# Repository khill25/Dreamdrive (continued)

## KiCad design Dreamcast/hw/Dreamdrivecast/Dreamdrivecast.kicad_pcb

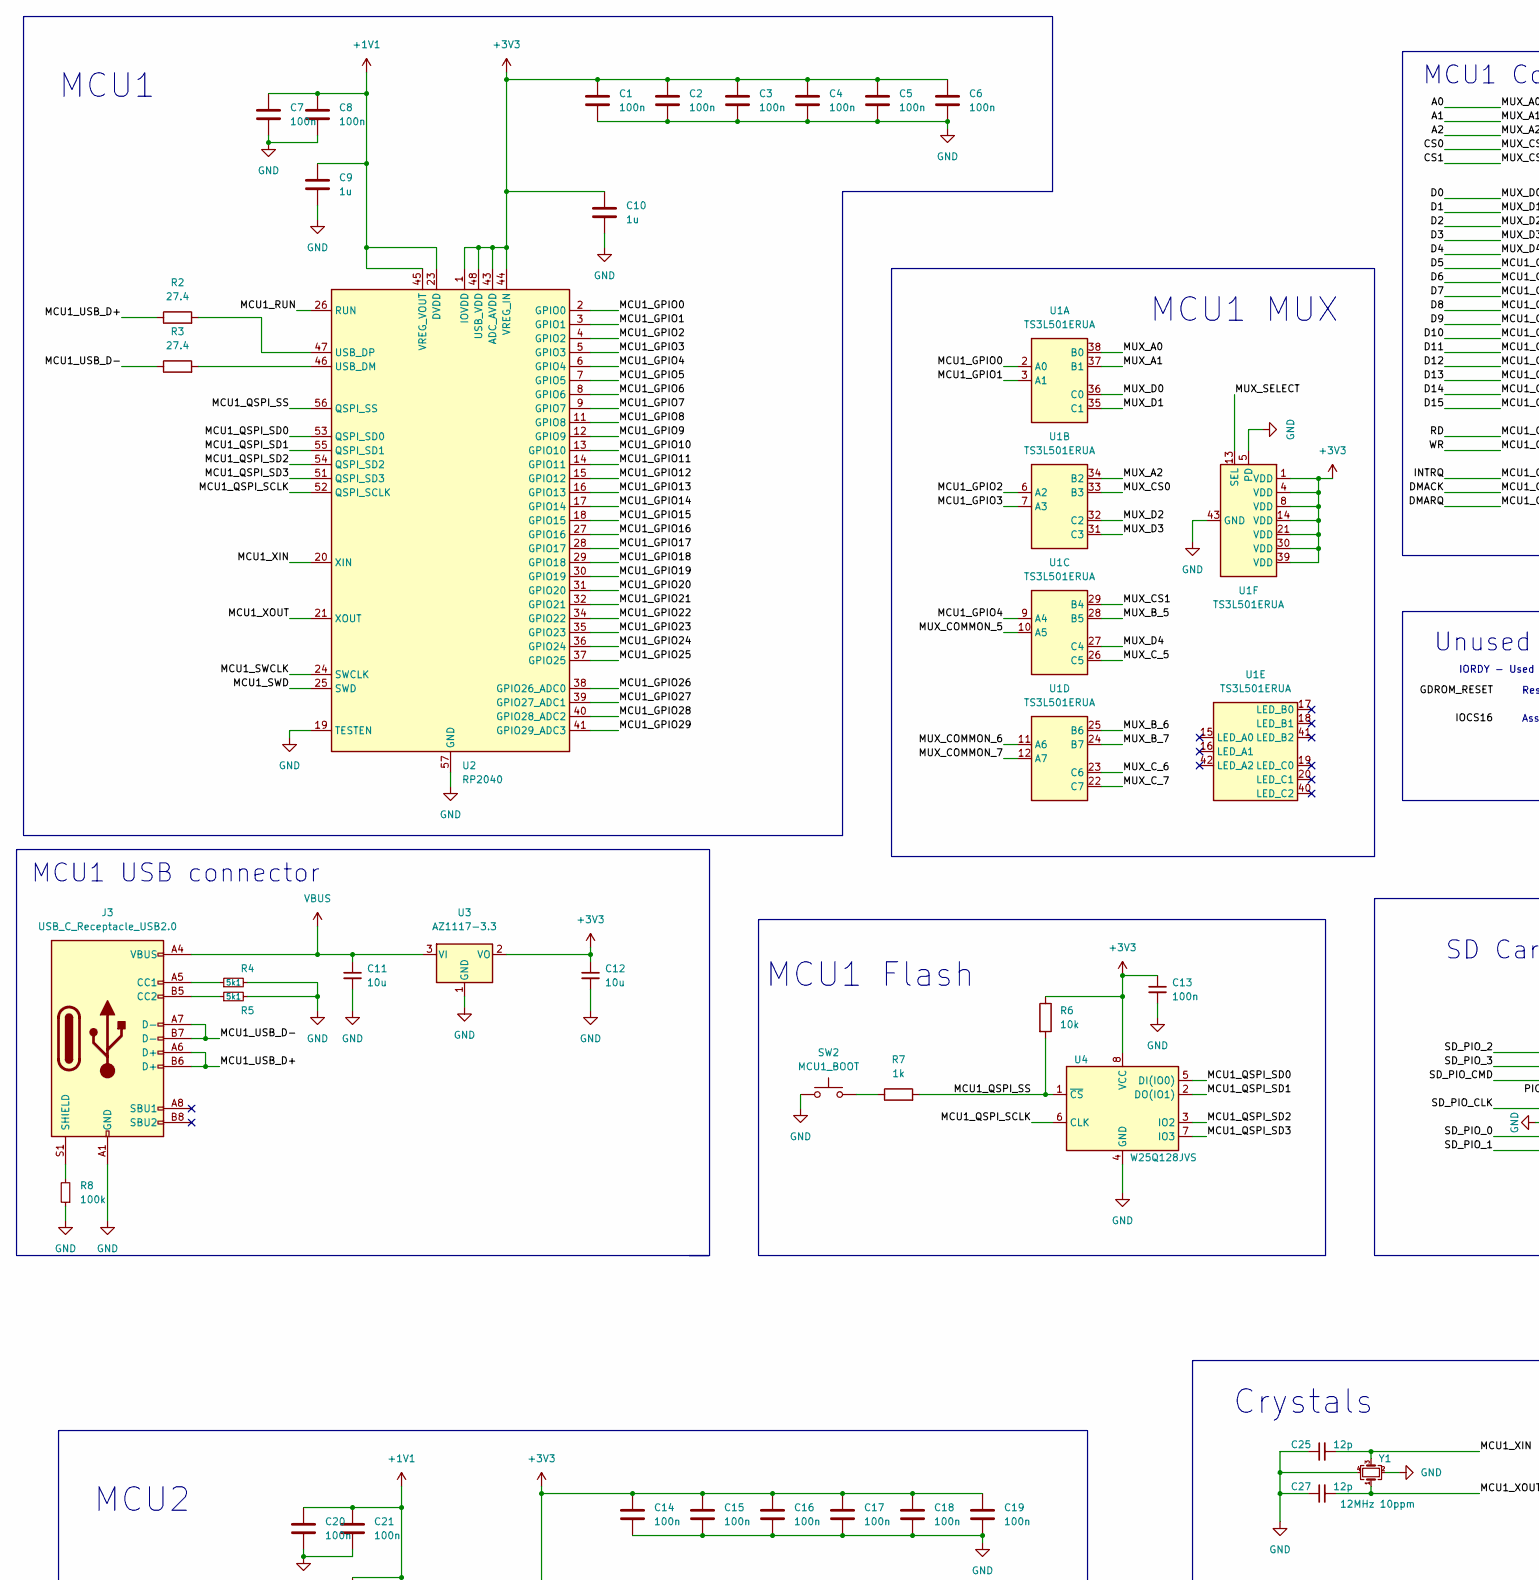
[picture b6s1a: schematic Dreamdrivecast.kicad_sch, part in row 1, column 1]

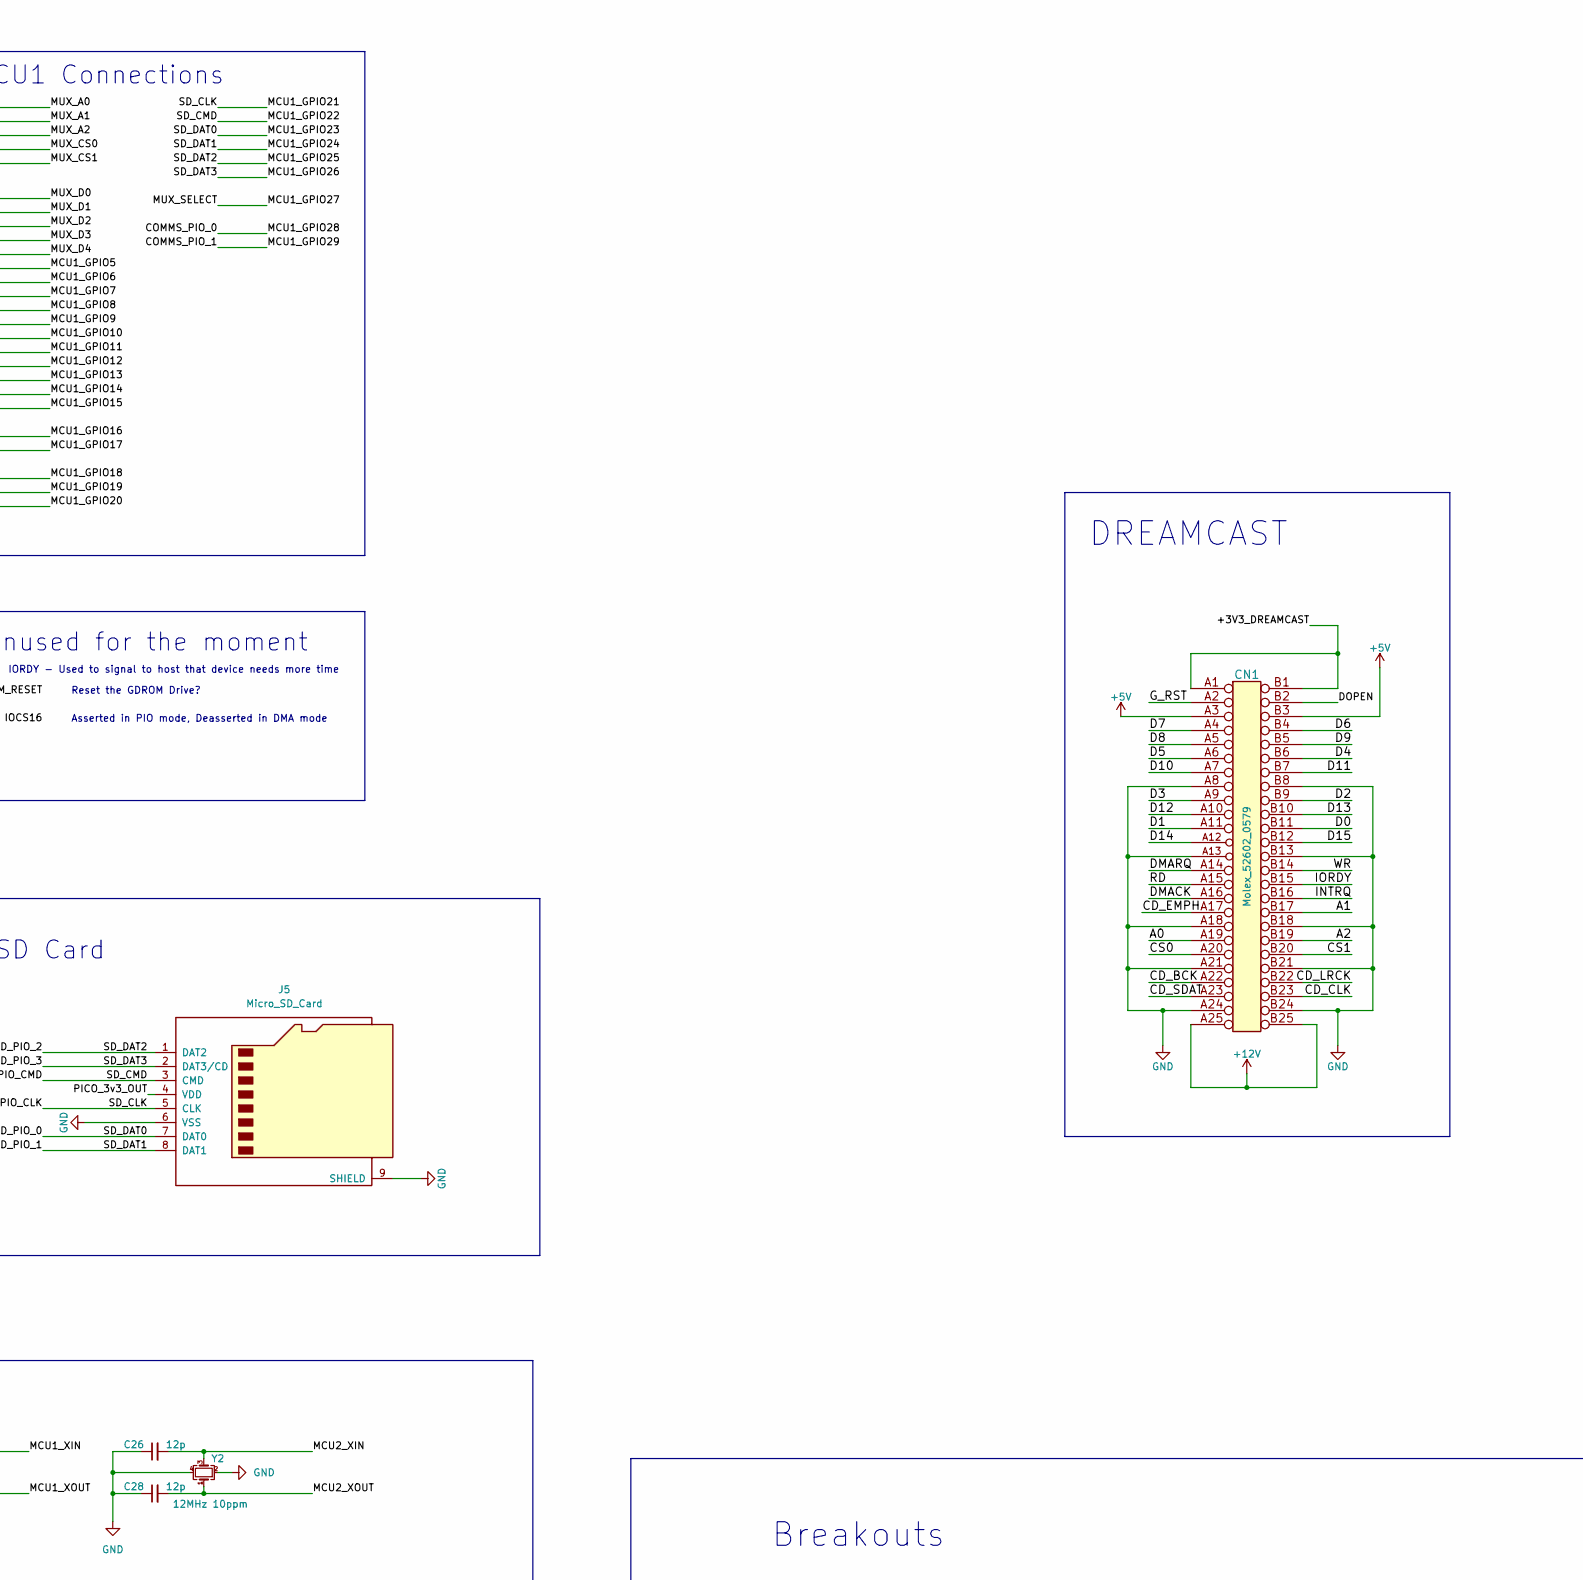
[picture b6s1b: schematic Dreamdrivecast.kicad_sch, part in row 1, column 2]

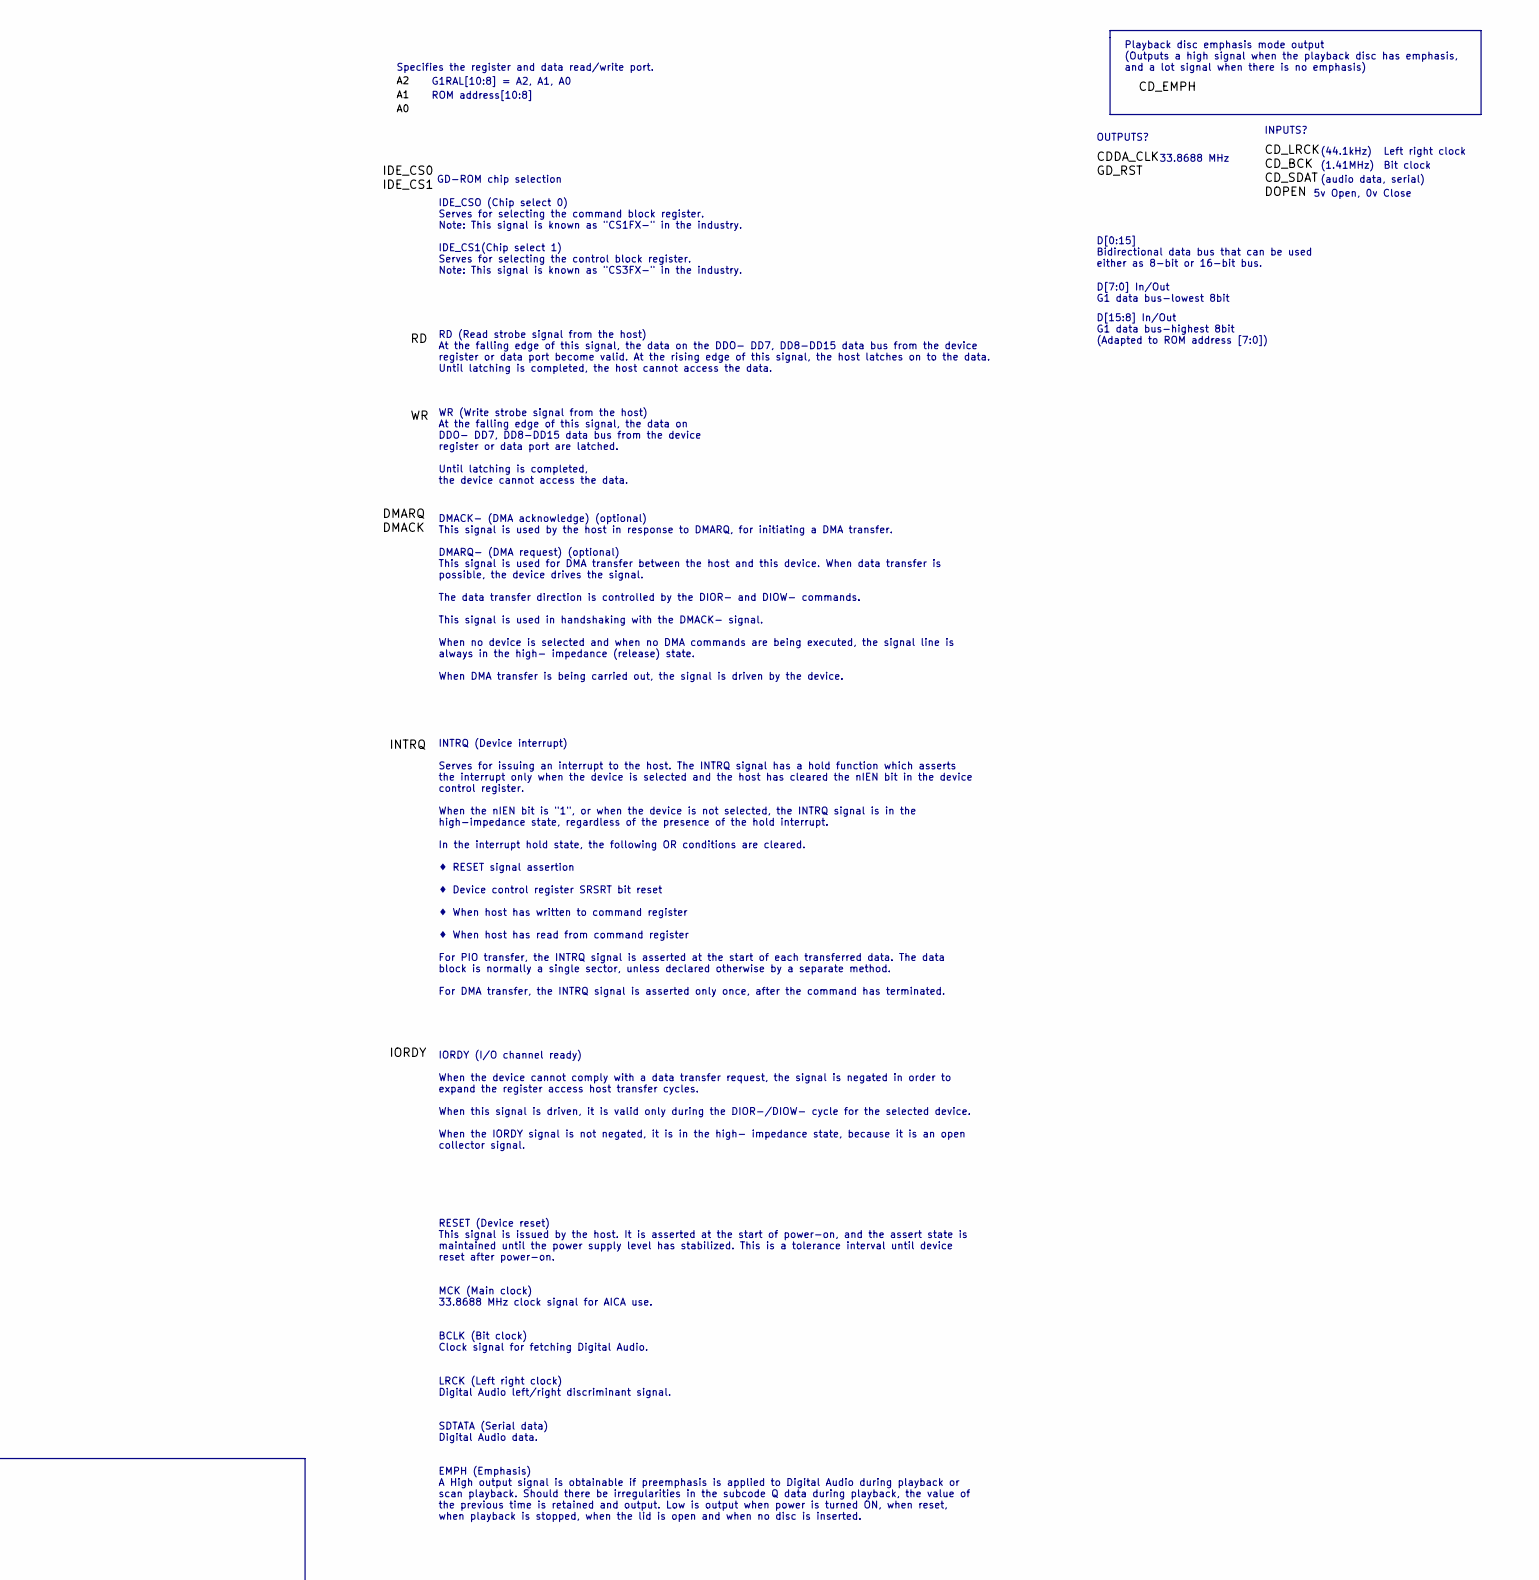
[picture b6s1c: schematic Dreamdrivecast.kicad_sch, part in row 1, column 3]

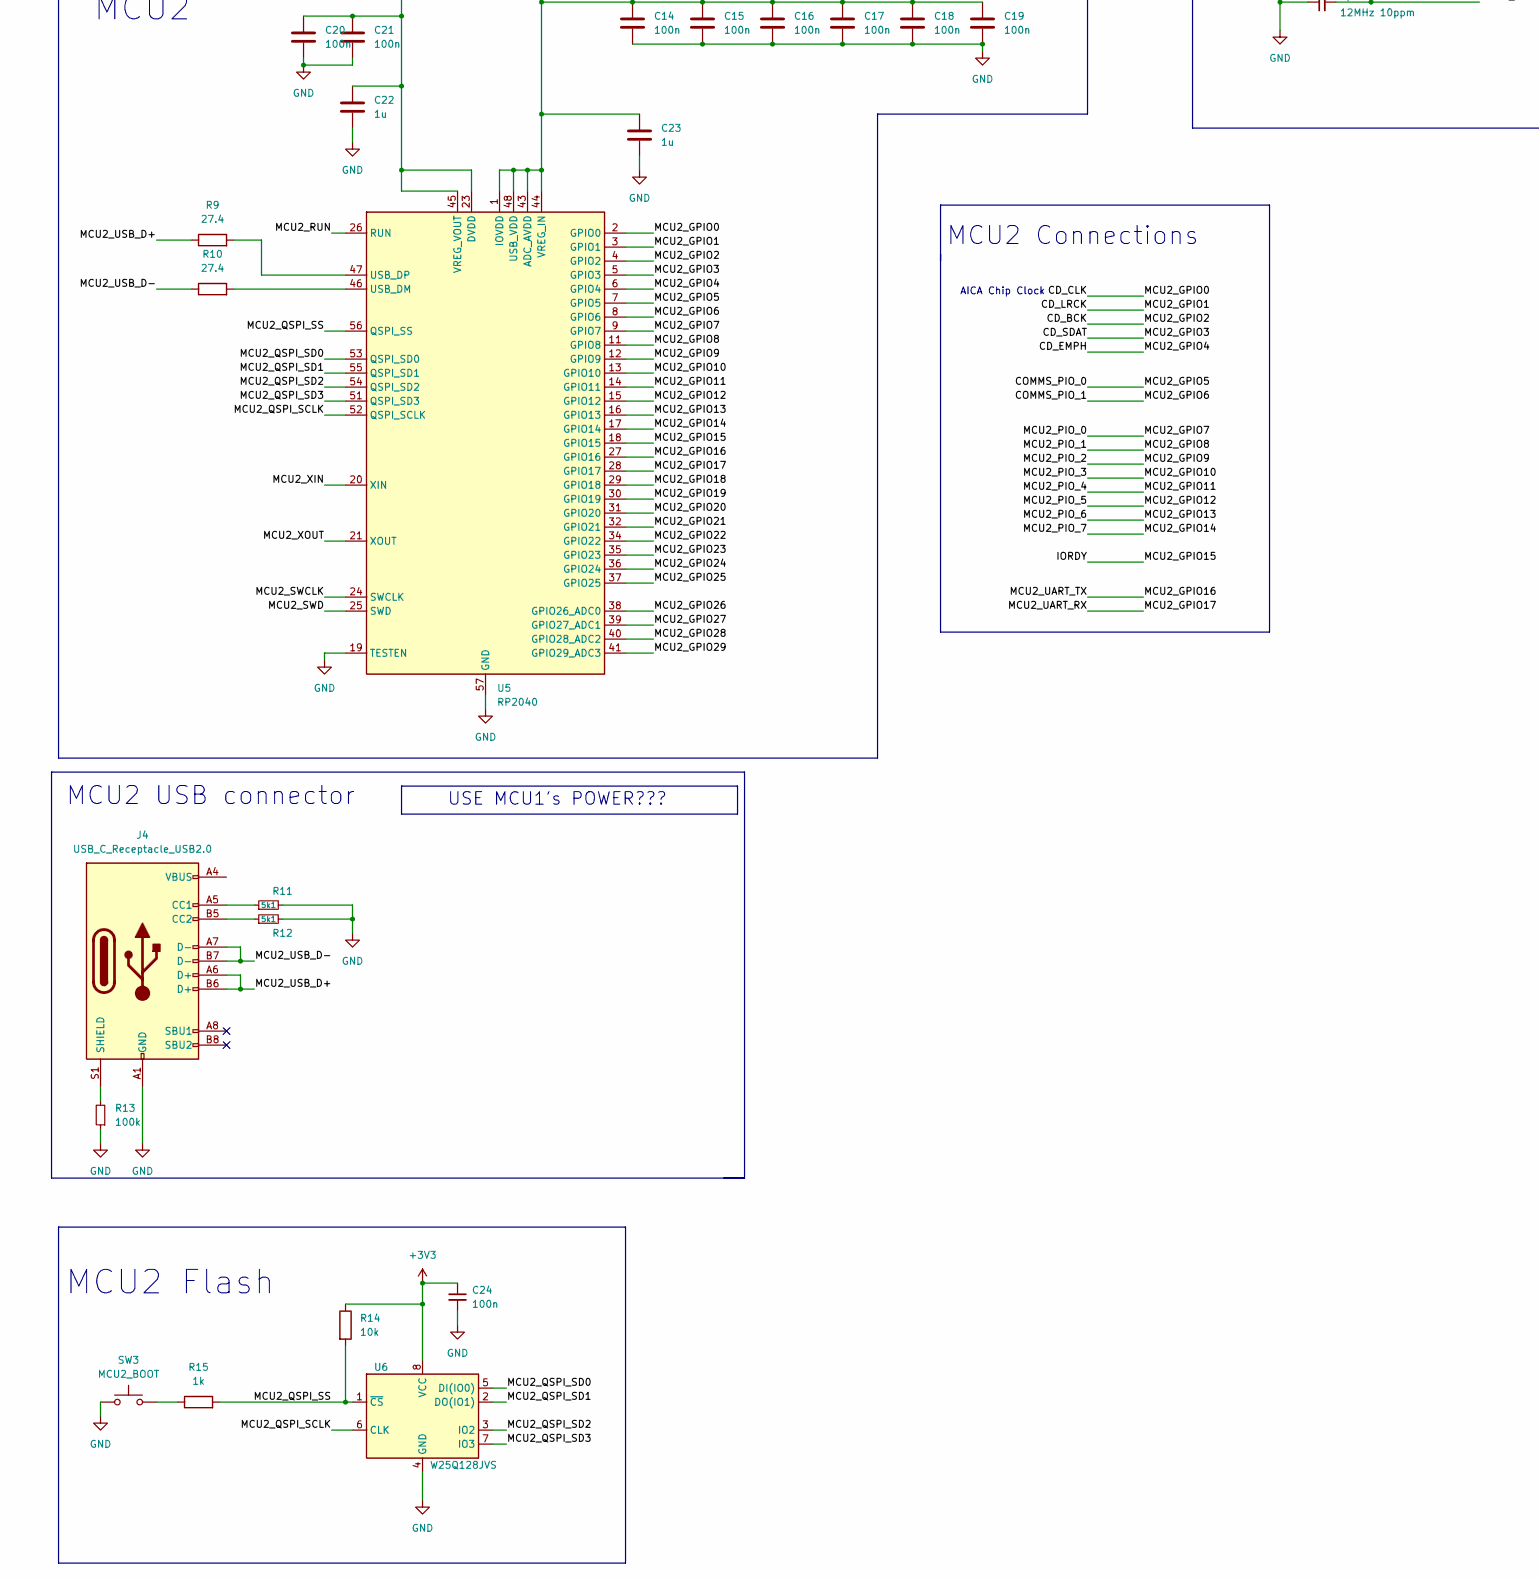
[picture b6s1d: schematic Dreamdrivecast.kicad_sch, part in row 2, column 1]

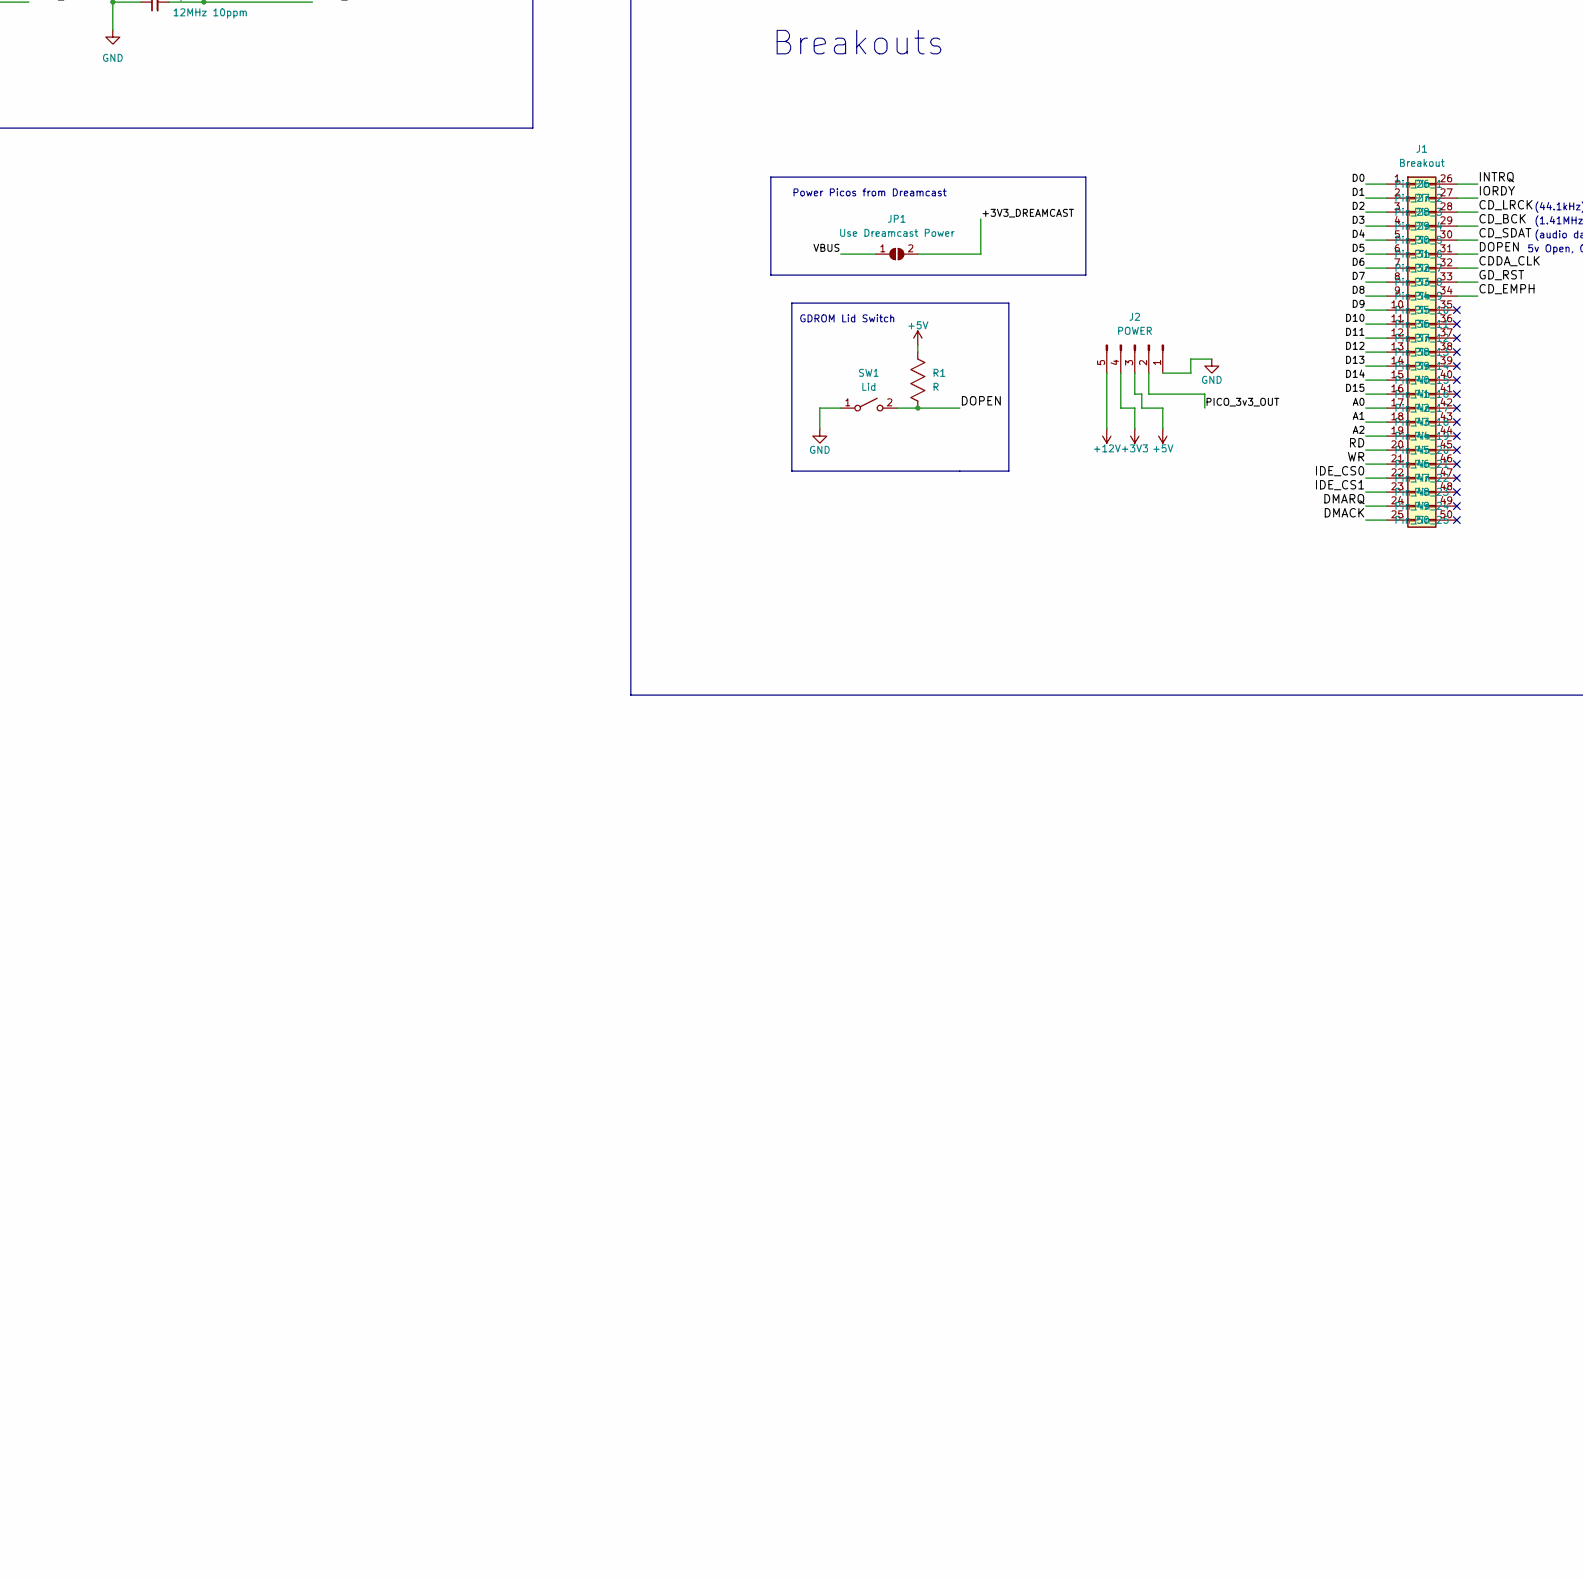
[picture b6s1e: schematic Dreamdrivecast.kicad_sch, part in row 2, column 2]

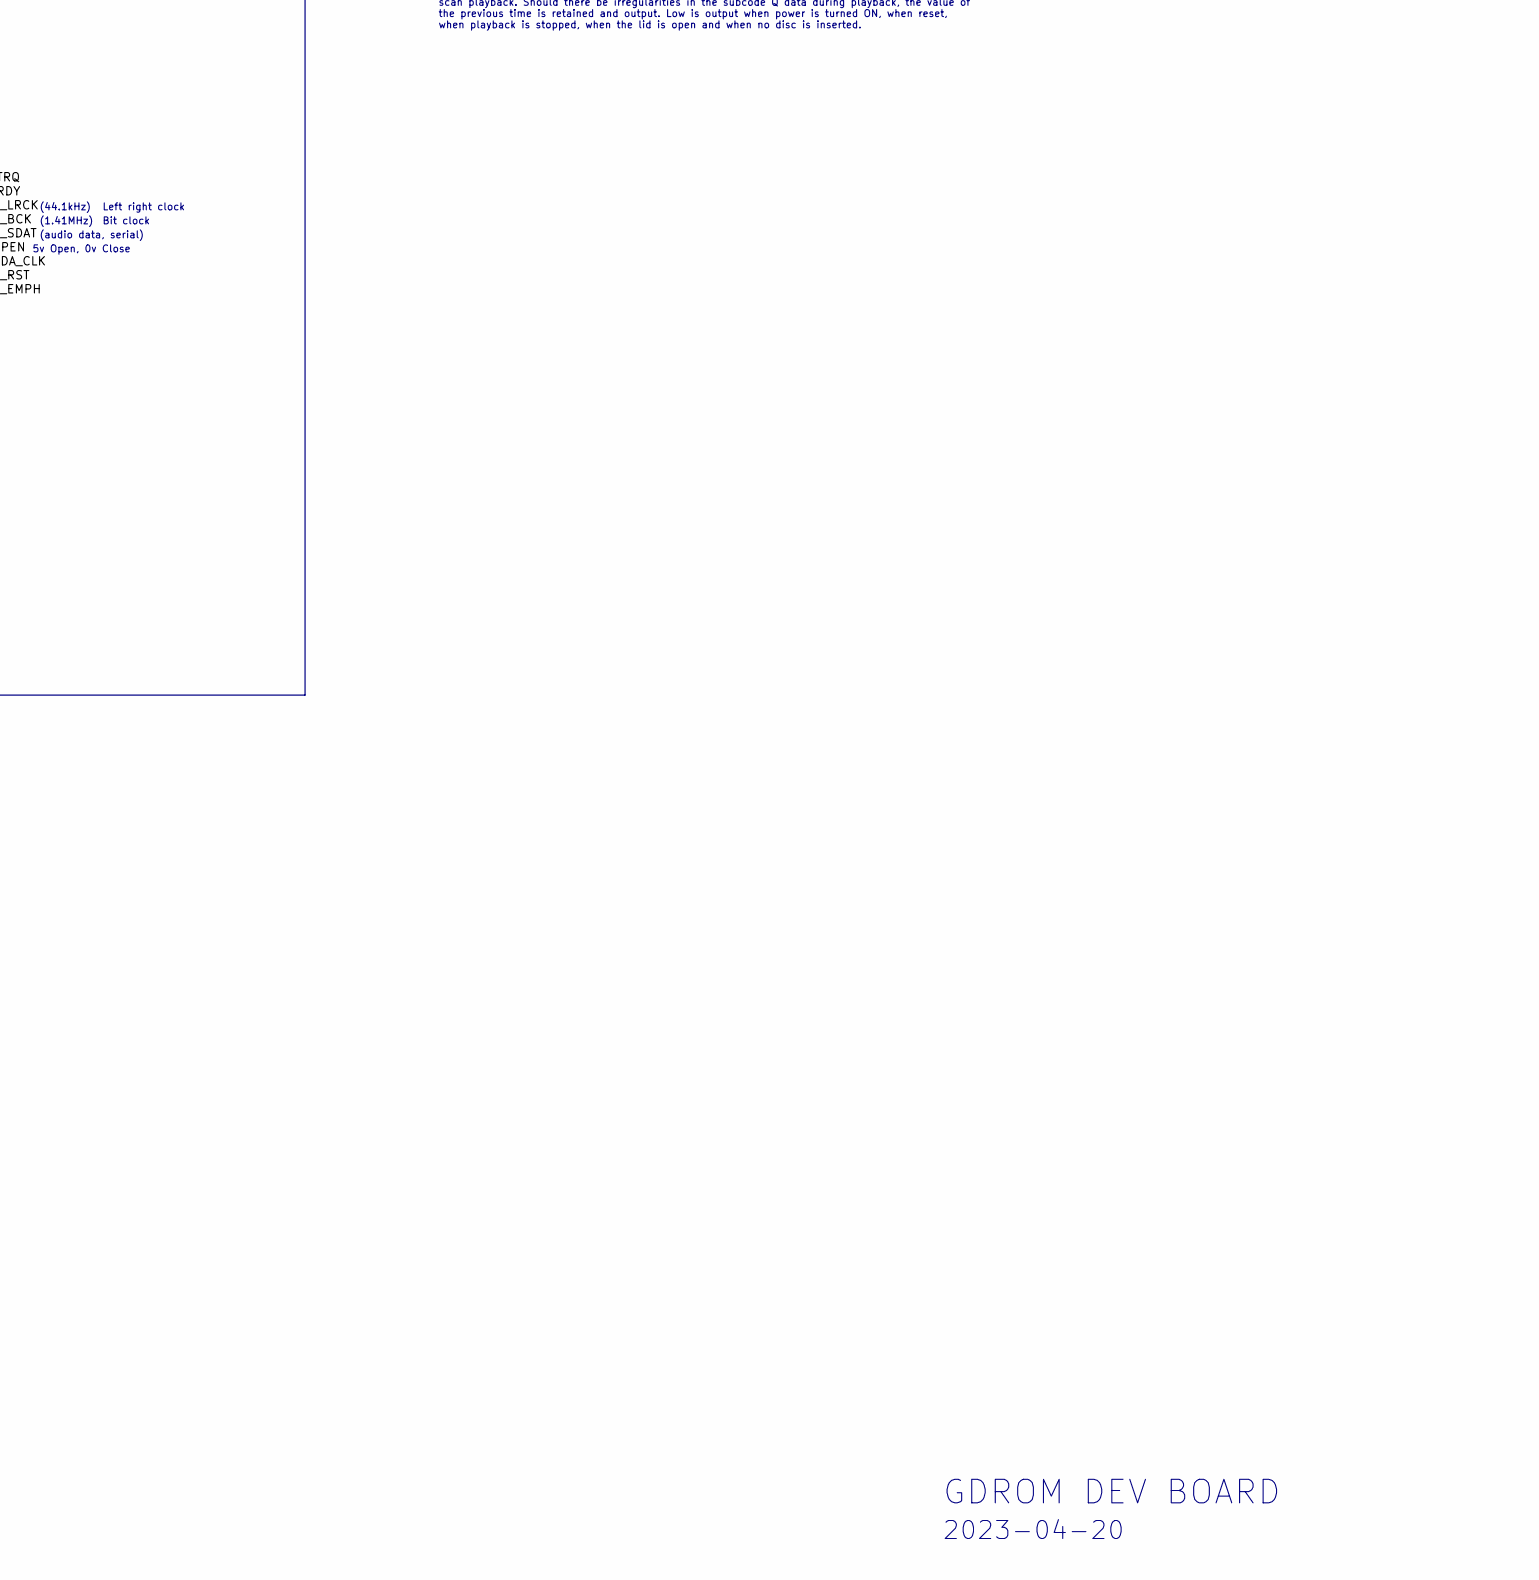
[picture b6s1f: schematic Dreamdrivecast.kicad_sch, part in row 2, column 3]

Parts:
C1, C2, C3, C4, C5, C6, C7, C8, C13, C14, C15, C16, C17, C18, C19, C20, C21, C24: 100n; C_0402_1005Metric; MPN CL05B104KO5NNNC; LCSC C1525
C9, C10, C22, C23: 1u; C_0402_1005Metric; MPN CL05A105KP5NNNC; LCSC C14445
C11, C12: 10u; C_0402_1005Metric; MPN CL05A106MP5NUNC; LCSC C315248
C25, C26, C27, C28: 12p; C_0402_1005Metric; MPN CC0402JRNPO9BN120; LCSC C106201
CN1: Molex_52602_0579; LCSC C588209
J1: Breakout; PinHeader_2x20_P2.54mm_Vertical_SMD
J2: POWER; PinHeader_1x05_P2.54mm_Vertical
J3, J4: USB_C_Receptacle_USB2.0; USB_C_Receptacle_Palconn_UTC16-G; MPN GT-USB-7010ASV; LCSC C2988369
J5: Micro_SD_Card; microSD_HC_Molex_104031-0811; MPN 1040310811; LCSC C585350
JP1: Use Dreamcast Power; SolderJumper-2_P1.3mm_Open_RoundedPad1.0x1.5mm
R1: R; R_Axial_DIN0207_L6.3mm_D2.5mm_P5.08mm_Vertical
R2, R3, R9, R10: 27.4; R_0402_1005Metric; MPN ARG02FTC27R4; LCSC C284479
R4, R5, R11, R12: 5k1; R_0402_1005Metric; MPN 0402WGF5101TCE; LCSC C25905
R6, R14: 10k; R_0402_1005Metric; MPN RC0402FR-0710KL; LCSC C60490
R7, R15: 1k; R_0402_1005Metric; MPN 0402WGJ0102TCE; LCSC C25543
R8, R13: 100k; R_0402_1005Metric; MPN RC0402FR-07100KL; LCSC C60491
SW1: Lid; SW_DIP_SPSTx01_Slide_9.78x4.72mm_W7.62mm_P2.54mm
SW2: MCU1_BOOT; SW_SPST_FSMSM; MPN TS-1092S-B3D2-G; LCSC C520860
SW3: MCU2_BOOT; SW_SPST_FSMSM; MPN TS-1092S-B3D2-G; LCSC C520860
U1: TS3L501ERUA; WQFN-42-1EP_3.5x9mm_P0.5mm_EP2.05x7.55mm; MPN TS3L501ERUAR; LCSC C2652454
U2, U5: RP2040; QFN-56-1EP_7x7mm_P0.4mm_EP3.2x3.2mm; MPN RP2040; LCSC C2040
U3: AZ1117-3.3; SOT-223; MPN AZ1117H-3.3TRG1; LCSC C110474
U4, U6: W25Q128JVS; SOIC-8_5.23x5.23mm_P1.27mm; MPN W25Q128JVSIQ; LCSC C97521
Y1, Y2: 12MHz 10ppm; Crystal_SMD_2520-4Pin_2.5x2.0mm; MPN XYDBPCNANF-12MHZ; LCSC C521567

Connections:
+1V1: C7.1, C8.1, C9.1, C20.1, C21.1, C22.1, U2.23 (DVDD), U2.45 (VREG_VOUT), U2.50 (DVDD), U5.23 (DVDD), U5.45 (VREG_VOUT), U5.50 (DVDD)
+3V3: C1.1, C2.1, C3.1, C4.1, C5.1, C6.1, C10.1, C12.1, C13.1, C14.1, C15.1, C16.1, C17.1, C18.1, C19.1, C23.1, C24.1, J2.4, R6.1, R14.1, U1.1 (VDD), U1.4 (VDD), U1.8 (VDD), U1.14 (VDD), U1.21 (VDD), U1.30 (VDD), U1.39 (VDD), U2.1 (IOVDD), U2.10 (IOVDD), U2.22 (IOVDD), U2.33 (IOVDD), U2.42 (IOVDD), U2.43 (ADC_AVDD), U2.44 (VREG_IN), U2.48 (USB_VDD), U2.49 (IOVDD), U3.2 (VO), U4.8 (VCC), U5.1 (IOVDD), U5.10 (IOVDD), U5.22 (IOVDD), U5.33 (IOVDD), U5.42 (IOVDD), U5.43 (ADC_AVDD), U5.44 (VREG_IN), U5.48 (USB_VDD), U5.49 (IOVDD), U6.8 (VCC)
+5V: CN1.A3, CN1.B3, J2.3, R1.1
+12V: CN1.A25, CN1.B25, J2.5
/+3V3_DREAMCAST: CN1.A1, CN1.B1, JP1.2 (B)
/A0: CN1.A19, J1.17, U1.38 (B0)
/A1: CN1.B17, J1.18, U1.37 (B1)
/A2: CN1.B19, J1.19, U1.34 (B2)
/CD_BCK: CN1.A22, J1.29, U5.4 (GPIO2)
/CD_CLK: CN1.B23, U5.2 (GPIO0)
/CD_EMPH: CN1.A17, J1.34, U5.6 (GPIO4)
/CD_LRCK: CN1.B22, J1.28, U5.3 (GPIO1)
/CD_SDAT: CN1.A23, J1.30, U5.5 (GPIO3)
/COMMS_PIO_0: U2.40 (GPIO28_ADC2), U5.7 (GPIO5)
/COMMS_PIO_1: U2.41 (GPIO29_ADC3), U5.8 (GPIO6)
/CS0: CN1.A20, U1.33 (B3)
/CS1: CN1.B20, U1.29 (B4)
/D0: CN1.B11, J1.1, U1.36 (C0)
/D1: CN1.A11, J1.2, U1.35 (C1)
/D2: CN1.B9, J1.3, U1.32 (C2)
/D3: CN1.A9, J1.4, U1.31 (C3)
/D4: CN1.B6, J1.5, U1.27 (C4)
/D5: CN1.A6, J1.6, U2.7 (GPIO5)
/D6: CN1.B4, J1.7, U2.8 (GPIO6)
/D7: CN1.A4, J1.8, U2.9 (GPIO7)
/D8: CN1.A5, J1.9, U2.11 (GPIO8)
/D9: CN1.B5, J1.10, U2.12 (GPIO9)
/D10: CN1.A7, J1.11, U2.13 (GPIO10)
/D11: CN1.B7, J1.12, U2.14 (GPIO11)
/D12: CN1.A10, J1.13, U2.15 (GPIO12)
/D13: CN1.B10, J1.14, U2.16 (GPIO13)
/D14: CN1.A12, J1.15, U2.17 (GPIO14)
/D15: CN1.B12, J1.16, U2.18 (GPIO15)
/DMACK: CN1.A16, J1.25, U2.30 (GPIO19)
/DMARQ: CN1.A14, J1.24, U2.31 (GPIO20)
/DOPEN: CN1.B2, J1.31, R1.2, SW1.2 (B)
/G_RST: CN1.A2
/INTRQ: CN1.B16, J1.26, U2.29 (GPIO18)
/IORDY: CN1.B15, J1.27, U5.18 (GPIO15)
/MCU1_GPIO0: U1.2 (A0), U2.2 (GPIO0)
/MCU1_GPIO1: U1.3 (A1), U2.3 (GPIO1)
/MCU1_GPIO2: U1.6 (A2), U2.4 (GPIO2)
/MCU1_GPIO3: U1.7 (A3), U2.5 (GPIO3)
/MCU1_GPIO4: U1.9 (A4), U2.6 (GPIO4)
/MCU1_GPIO16: CN1.A15, J1.20, U2.27 (GPIO16)
/MCU1_GPIO17: CN1.B14, J1.21, U2.28 (GPIO17)
/MCU1_GPIO21: J5.5 (CLK), U2.32 (GPIO21)
/MCU1_GPIO22: J5.3 (CMD), U2.34 (GPIO22)
/MCU1_GPIO23: J5.7 (DAT0), U2.35 (GPIO23)
/MCU1_GPIO24: J5.8 (DAT1), U2.36 (GPIO24)
/MCU1_GPIO25: J5.1 (DAT2), U2.37 (GPIO25)
/MCU1_GPIO26: J5.2 (DAT3/CD), U2.38 (GPIO26_ADC0)
/MCU1_GPIO27: U1.13 (SEL), U2.39 (GPIO27_ADC1)
/MCU1_QSPI_SCLK: U2.52 (QSPI_SCLK), U4.6 (CLK)
/MCU1_QSPI_SD0: U2.53 (QSPI_SD0), U4.5 (DI(IO0))
/MCU1_QSPI_SD1: U2.55 (QSPI_SD1), U4.2 (DO(IO1))
/MCU1_QSPI_SD2: U2.54 (QSPI_SD2), U4.3 (IO2)
/MCU1_QSPI_SD3: U2.51 (QSPI_SD3), U4.7 (IO3)
/MCU1_QSPI_SS: R6.2, R7.2, U2.56 (QSPI_SS), U4.1 (~CS)
/MCU1_RUN: U2.26 (RUN); also elsewhere on the board
/MCU1_SWCLK: U2.24 (SWCLK)
/MCU1_SWD: U2.25 (SWD)
/MCU1_USB_D+: J3.A6 (D+), J3.B6 (D+), R2.1
/MCU1_USB_D-: J3.A7 (D-), J3.B7 (D-), R3.1
/MCU1_XIN: C25.2, U2.20 (XIN), Y1.3
/MCU1_XOUT: C27.2, U2.21 (XOUT), Y1.1
/MCU2_GPIO7: U5.9 (GPIO7)
/MCU2_GPIO8: U5.11 (GPIO8)
/MCU2_GPIO9: U5.12 (GPIO9)
/MCU2_GPIO10: U5.13 (GPIO10)
/MCU2_GPIO11: U5.14 (GPIO11)
/MCU2_GPIO12: U5.15 (GPIO12)
/MCU2_GPIO13: U5.16 (GPIO13)
/MCU2_GPIO14: U5.17 (GPIO14)
/MCU2_GPIO16: U5.27 (GPIO16)
/MCU2_GPIO17: U5.28 (GPIO17)
/MCU2_GPIO18: U5.29 (GPIO18)
/MCU2_GPIO19: U5.30 (GPIO19)
/MCU2_GPIO20: U5.31 (GPIO20)
/MCU2_GPIO21: U5.32 (GPIO21)
/MCU2_GPIO22: U5.34 (GPIO22)
/MCU2_GPIO23: U5.35 (GPIO23)
/MCU2_GPIO24: U5.36 (GPIO24)
/MCU2_GPIO25: U5.37 (GPIO25)
/MCU2_GPIO26: U5.38 (GPIO26_ADC0)
/MCU2_GPIO27: U5.39 (GPIO27_ADC1)
/MCU2_GPIO28: U5.40 (GPIO28_ADC2)
/MCU2_GPIO29: U5.41 (GPIO29_ADC3)
/MCU2_QSPI_SCLK: U5.52 (QSPI_SCLK), U6.6 (CLK)
/MCU2_QSPI_SD0: U5.53 (QSPI_SD0), U6.5 (DI(IO0))
/MCU2_QSPI_SD1: U5.55 (QSPI_SD1), U6.2 (DO(IO1))
/MCU2_QSPI_SD2: U5.54 (QSPI_SD2), U6.3 (IO2)
/MCU2_QSPI_SD3: U5.51 (QSPI_SD3), U6.7 (IO3)
/MCU2_QSPI_SS: R14.2, R15.2, U5.56 (QSPI_SS), U6.1 (~CS)
/MCU2_RUN: U5.26 (RUN); also elsewhere on the board
/MCU2_SWCLK: U5.24 (SWCLK)
/MCU2_SWD: U5.25 (SWD)
/MCU2_USB_D+: J4.A6 (D+), J4.B6 (D+), R9.1
/MCU2_USB_D-: J4.A7 (D-), J4.B7 (D-), R10.1
/MCU2_XIN: C26.2, U5.20 (XIN), Y2.3
/MCU2_XOUT: C28.2, U5.21 (XOUT), Y2.1
/MUX_B_5: U1.28 (B5)
/MUX_B_6: U1.25 (B6)
/MUX_B_7: U1.24 (B7)
/MUX_COMMON_5: U1.10 (A5)
/MUX_COMMON_6: U1.11 (A6)
/MUX_COMMON_7: U1.12 (A7)
/MUX_C_5: U1.26 (C5)
/MUX_C_6: U1.23 (C6)
/MUX_C_7: U1.22 (C7)
/PICO_3v3_OUT: J2.2, J5.4 (VDD)
GND: C1.2, C2.2, C3.2, C4.2, C5.2, C6.2, C7.2, C8.2, C9.2, C10.2, C11.2, C12.2, C13.2, C14.2, C15.2, C16.2, C17.2, C18.2, C19.2, C20.2, C21.2, C22.2, C23.2, C24.2, C25.1, C26.1, C27.1, C28.1, CN1.A8, CN1.A13, CN1.A18, CN1.A21, CN1.A24, CN1.B8, CN1.B13, CN1.B18, CN1.B21, CN1.B24, J2.1, J3.A1 (GND), J3.A12 (GND), J3.B1 (GND), J3.B12 (GND), J4.A1 (GND), J4.A12 (GND), J4.B1 (GND), J4.B12 (GND), J5.6 (VSS), J5.9 (SHIELD), R4.2, R5.2, R8.1, R11.2, R12.2, R13.1, SW1.1 (A), SW2.1, SW3.1, U1.5 (PD), U1.43 (GND), U2.19 (TESTEN), U2.57 (GND), U3.1 (GND), U4.4 (GND), U5.19 (TESTEN), U5.57 (GND), U6.4 (GND), Y1.2, Y1.4, Y2.2, Y2.4; also elsewhere on the board
unnamed: J3.A5 (CC1), R4.1
unnamed: J3.B5 (CC2), R5.1
unnamed: J3.S1 (SHIELD), R8.2
unnamed: J4.A4 (VBUS), J4.A9 (VBUS), J4.B4 (VBUS), J4.B9 (VBUS)
unnamed: J4.A5 (CC1), R11.1
unnamed: J4.B5 (CC2), R12.1
unnamed: J4.S1 (SHIELD), R13.2
unnamed: R2.2, U2.47 (USB_DP)
unnamed: R3.2, U2.46 (USB_DM)
unnamed 121: R7.1, SW2.2; also elsewhere on the board
unnamed: R9.2, U5.47 (USB_DP)
unnamed: R10.2, U5.46 (USB_DM)
unnamed 124: R15.1, SW3.2; also elsewhere on the board
VBUS: C11.1, J3.A4 (VBUS), J3.A9 (VBUS), J3.B4 (VBUS), J3.B9 (VBUS), JP1.1 (A), U3.3 (VI)

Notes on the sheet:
(1.41MHz)
Reset the GDROM Drive?
RD (Read strobe signal from the host) At the falling edge of this signal, the data on the DDO- DD7, DD8-DD15 data bus from the device register or data port become valid. At the rising edge of this signal, the host latches on to the data. Until latching is completed, the host cannot access the data.
5v Open, 0v Close
(44.1kHz)
WR (Write strobe signal from the host) At the falling edge of this signal, the data on DDO- DD7, DD8-DD15 data bus from the device register or data port are latched. Until latching is completed, the device cannot access the data.
IORDY - Used to signal to host that device needs more time
Left right clock
Unused for the moment
ROM address[10:8]
SD Card
USE MCU1's POWER???
GDROM DEV BOARD
MCU2 Connections
MCU2 Flash
GD-ROM chip selection
Specifies the register and data read/write port.
Playback disc emphasis mode output (Outputs a high signal when the playback disc has emphasis, and a lot signal when there is no emphasis)
MCU1
MCU2
Breakouts
MCU1 USB connector
Bit clock
D[15:8] In/Out G1 data bus-highest 8bit (Adapted to ROM address [7:0])
MCU1 Connections
DMACK- (DMA acknowledge) (optional) This signal is used by the host in response to DMARQ, for initiating a DMA transfer. DMARQ- (DMA request) (optional) This signal is used for DMA transfer between the host and this device. When data transfer is possible, the device drives the signal. The data tran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
(audio data, serial)
MCU1 Flash
OUTPUTS?
GDROM Lid Switch
2023-04-20
INTRQ (Device interrupt) Serves for issuing an interrupt to the host. The INTRQ signal has a hold function which asserts the interrupt only when the device is selected and the host has cleared the nIEN bit in the device control register. When the nIEN bit is "1", or when the device is not selected,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
33.8688 MHz
Power Picos from Dreamcast
MCU2 USB connector
MCU1 MUX
D[0:15] Bidirectional data bus that can be used either as 8-bit or 16-bit bus.
IDE_CSO (Chip select 0) Serves for selecting the command block register. Note: This signal is known as "CS1FX-" in the industry. IDE_CS1(Chip select 1) Serves for selecting the control block register. Note: This signal is known as "CS3FX-" in the industry.
AICA Chip Clock
D[7:0] In/Out G1 data bus-lowest 8bit

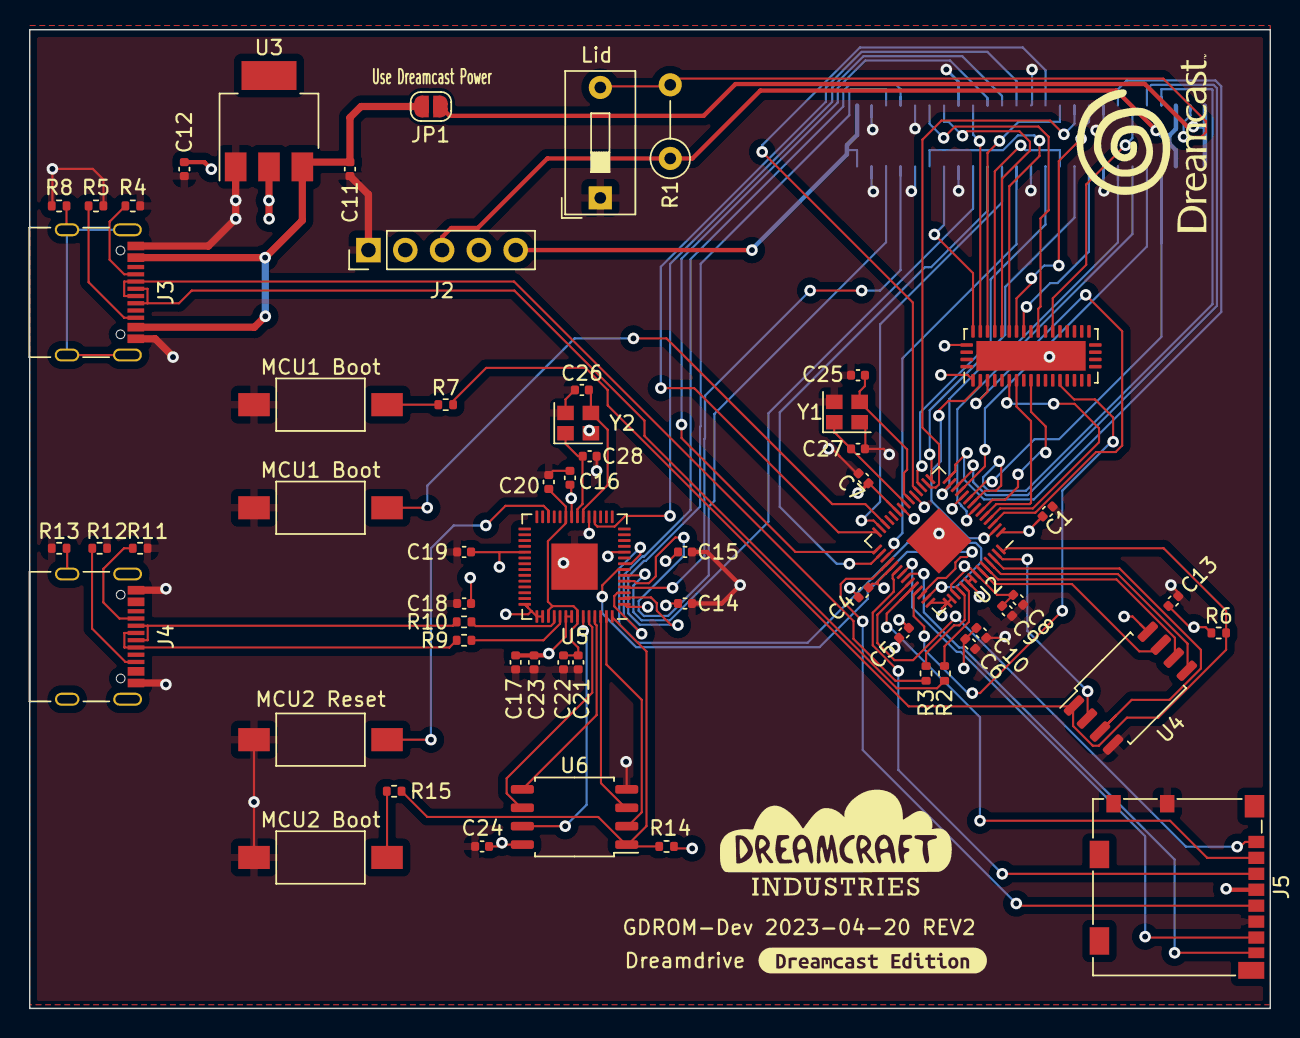
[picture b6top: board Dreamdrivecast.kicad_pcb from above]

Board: 4 copper layers, 85.6 x 67.5 mm, 62 parts (1 on the bottom side), 90 nets.

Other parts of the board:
DREAMCRAFT_LOGO: LOGO
MCU1 Boot, MCU1 Boot#2, MCU2 Reset: MCU1_BOOT; SW_SPST_FSMSM
MCU2 Boot: MCU2_BOOT; SW_SPST_FSMSM
kibuzzard-63F149CE: DDR_DREAMCAST; kibuzzard-63F149CE

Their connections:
/MCU1_RUN: MCU1 Boot.2; also elsewhere on the board
/MCU2_RUN: MCU2 Reset.1; also elsewhere on the board
GND: MCU1 Boot.1, MCU1 Boot#2.1, MCU2 Boot.1, MCU2 Reset.2; also elsewhere on the board
unnamed 121: MCU1 Boot#2.2; also elsewhere on the board
unnamed 124: MCU2 Boot.2; also elsewhere on the board

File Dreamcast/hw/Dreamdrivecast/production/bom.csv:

Designator,Footprint,Quantity,Value,LCSC Part #
"C1, C13, C14, C15, C16, C17, C18, C19, C20, C21, C24, C4, C5, C6, C7, C8",0402,16,100n,C1525
"C10, C22, C23, C9",0402,4,1u,C14445
"C11, C12",0402,2,10u,C315248
"C25, C26, C27, C28",0402,4,12p,C106201
CN1,Molex_52602_0579,1,Molex_52602_0579,C588209
"J3, J4",USB_C_Receptacle_Palconn_UTC16-G,2,USB_C_Receptacle_USB2.0,C2988369
J5,microSD_HC_Molex_104031-0811,1,Micro_SD_Card,C585350
"MCU1 Boot_2, MCU1 Boot, MCU2 Reset",SW_SPST_FSMSM,3,MCU1_BOOT,C520860
MCU2 Boot,SW_SPST_FSMSM,1,MCU2_BOOT,C520860
"R10, R2, R3, R9",0402,4,27.4,C284479
"R11, R12, R4, R5",0402,4,5k1,C25905
"R13, R8",0402,2,100k,C60491
"R14, R6",0402,2,10k,C60490
"R15, R7",0402,2,1k,C25543
U1,WQFN-42-1EP_3.5x9mm_P0.5mm_EP2.05x7.55mm,1,TS3L501ERUA,C2652454
"U2, U5",QFN-56-1EP_7x7mm_P0.4mm_EP3.2x3.2mm,2,RP2040,C2040
U3,SOT-223,1,AZ1117-3.3,C110474
"U4, U6",SOIC-8_5.23x5.23mm_P1.27mm,2,W25Q128JVS,C97521
"Y1, Y2",Crystal_SMD_2520-4Pin_2.5x2.0mm,2,12MHz 10ppm,C521567
